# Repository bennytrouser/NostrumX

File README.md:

# NostrumX
A 32 key ergonomic split keyboard using Seeed Xiao BLE

This keyboard is a variation on my original [Nostrum](https://github.com/bennytrouser/nostrum) using a Seeeduino Xiao BLE with the battery mounted under the PCB within the case. Not designed to be used without the case.

The aim was to create a case based board while maintaining as much of the original shape and clean lines of the original nostrum pcb. 

- 3° Splay on pinky and ring columns
- Choc V1 switch compatible (hotswap or soldered). Hotswap recomennded as the switch plate is integrated into the case.
- Custom mildly tented case including switch sliders.
- MCU not socketed, SMD soldered only.
- Created with the [ergogen](https://github.com/ergogen/ergogen) and KiCad8. Case files created with Autodesk Fusion360.
- Firmware using ZMK, including the RGB Widget module from [Caksoylar](https://github.com/caksoylar/zmk-rgbled-widget)
- Inspiration from the [Hummingbird](https://github.com/PJE66/hummingbird) style [Berylline](https://github.com/jcmkk3/trochilidae#berylline) by [jcmkk3](https://github.com/jcmkk3)
- Mousebite breakaway tabs design are inspired by Sadekbaroudi's [bykeeb](https://github.com/sadekbaroudi/bykeeb)

## PCB

## Parts
The case is designed to be fastened from the underside using M1.5x6mm self tapping screws. Feet used are 10x3x1.5mm and 14x3x1.5mm. Left side has space to fit a lipo Battery 402030(180mah). Due to constraints, the right side will need a narrower battery if using hotswap. For my build, I used a 401322 (120mah) but a different size may fit. Example parts listed below. Source your switches and sockets and MCUs where available.

| Part  | Link |
| ------------- | ------------- |
| Battery 402030 | https://www.ebay.co.uk/itm/355875616696 |
| Battery 401322 | https://www.ebay.co.uk/itm/195234785175 |
| Self tapping Screws M1.5x6mm | https://www.aliexpress.com/item/1005005469153402.html |
| SMD diodes SOD-123 1N4148W T4 | https://www.aliexpress.com/item/32948518338.html |
| 1.5mm Fibreoptic cable (for led shinethrough) | https://www.aliexpress.com/item/1005005886250822.html |
| Reset button TL3342 | https://www.aliexpress.com/item/1005007506687094.html |
| Power switch PCM12 | https://www.aliexpress.com/item/32912838968.html |
| Feet | https://www.aliexpress.com/item/1005006691343859.html |

## Case files
Designed in Fusion360. 3d printed. Recommended to print the top case with face down for texured finish. There are two different bottoms, with or without a hole for a reset switch depending on if you want to use one.

The Switch bits need to be fitted before installing the pcb and are a tight fit. Also may require a bit of jiggling to get the slider to seat correctly on install.

The holes on the top of the case allow the charge led and the user led to shine through. I have used fibre optic cable in these holes but it is optional and a tight fit that may require slight enlargement with a screwdriver or small drillbit for the cable to slide in. Any larger in the file and it's a little loose.

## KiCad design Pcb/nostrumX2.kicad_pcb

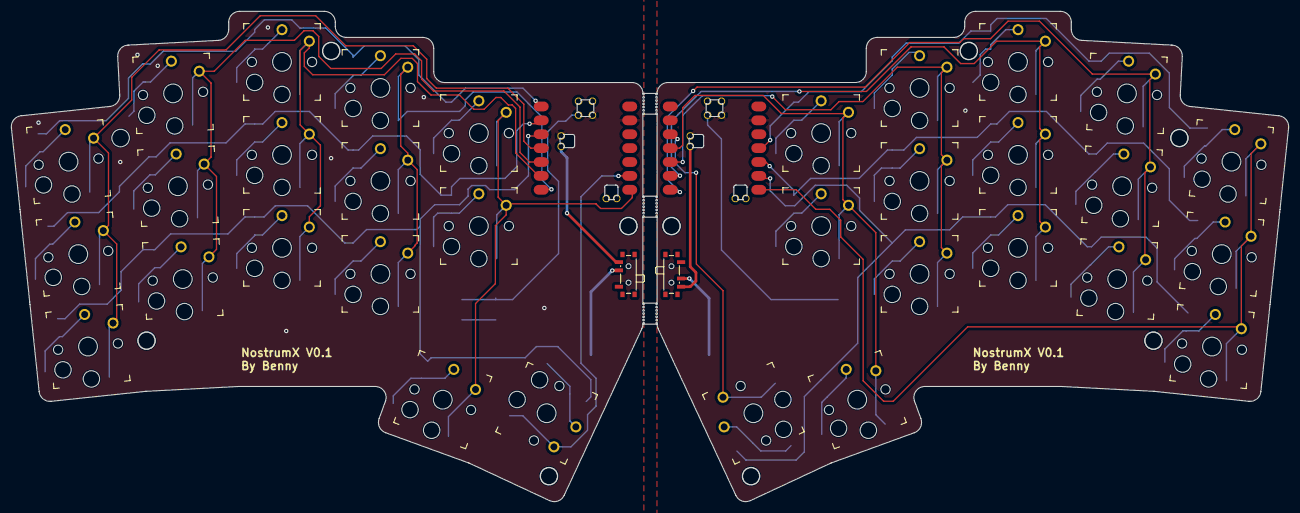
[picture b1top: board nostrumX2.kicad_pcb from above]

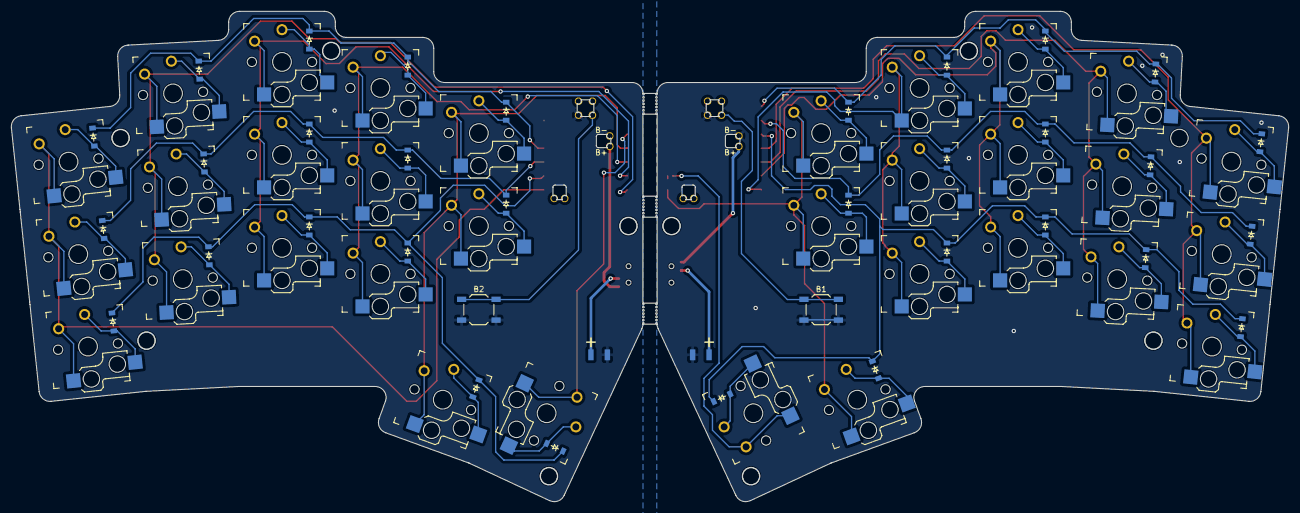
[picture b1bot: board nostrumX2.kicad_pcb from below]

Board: 2 copper layers, 233.6 x 89.7 mm, 79 parts (34 on the bottom side), 52 nets.

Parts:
B1, B2: SW_SPST_TL3342
D1, D2, D3, D4, D5, D6, D7, D8, D9, D10, D11, D12, D13, D14, D15, D16, D17, D18, D19, D20, D21, D22, D23, D24, D25, D26, D27, D28, D29, D30, D31, D32: ComboDiode
LH1, LH2, LH3: Breakaway Tabs; Breakaway_Tabs_Med
Mount: MountingHole_3.2mm_M3
PAD1, PAD2, PAD3, PAD4: SMDPad
RH1, RH2, RH3: Breakaway Tabs; Breakaway_Tabs_Med
S1, S2, S3, S4, S5, S6, S7, S8, S9, S10, S11, S12, S13, S14, S15, S16, S17, S18, S19, S20, S21, S22, S23, S24, S25, S26, S27, S28, S29, S30, S31, S32: PG1350
SW1, SW2: SW_SPDT_PCM12

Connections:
C0: S1.1, S2.1, S3.1
C1: S4.1, S5.1, S6.1
C2: S7.1, S8.1, S9.1
C3: S10.1, S11.1, S12.1
C4: S13.1, S14.1, S29.1
GND: B1.2, PAD2.1
MC0: S15.1, S16.1, S17.1
MC1: S18.1, S19.1, S20.1
MC2: S21.1, S22.1, S23.1
MC3: S24.1, S25.1, S26.1
MC4: S27.1, S28.1, S31.1
MGND: B2.2, PAD4.1
MR0: D19.1, D22.1, D25.1, D28.1, D30.1
MR1: D18.1, D21.1, D24.1, D27.1, D29.1
MR2: D17.1, D20.1, D23.1, D26.1, D31.1, D32.1
Mpos: PAD3.1, SW2.2
R0: D3.1, D6.1, D9.1, D12.1, D14.1
R1: D2.1, D5.1, D8.1, D11.1, D13.1
R2: D1.1, D4.1, D7.1, D10.1, D15.1, D16.1
index_bottom: D10.2, S10.2
index_home: D11.2, S11.2
index_top: D12.2, S12.2
inner_bottom: D13.2, S13.2
inner_home: D14.2, S14.2
left_home: D15.2, S29.2
middle_bottom: D7.2, S7.2
middle_home: D8.2, S8.2
middle_top: D9.2, S9.2
mirror_index_bottom: D26.2, S24.2
mirror_index_home: D27.2, S25.2
mirror_index_top: D28.2, S26.2
mirror_inner_bottom: D29.2, S27.2
mirror_inner_home: D30.2, S28.2
mirror_left_home: D31.2, S31.2
mirror_middle_bottom: D23.2, S21.2
mirror_middle_home: D24.2, S22.2
mirror_middle_top: D25.2, S23.2
mirror_pinky_bottom: D17.2, S15.2
mirror_pinky_home: D18.2, S16.2
mirror_pinky_top: D19.2, S17.2
mirror_right_home: D32.2, S32.2
mirror_ring_bottom: D20.2, S18.2
mirror_ring_home: D21.2, S19.2
mirror_ring_top: D22.2, S20.2
pinky_bottom: D1.2, S1.2
pinky_home: D2.2, S2.2
pinky_top: D3.2, S3.2
pos: PAD1.1, SW1.2
right_home: D16.2, S30.2
ring_bottom: D4.2, S4.2
ring_home: D5.2, S5.2
ring_top: D6.2, S6.2

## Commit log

2024-08-13 Updated files and readme
2024-08-13 update RM
2024-08-15 Final update
2024-08-15 add sadek ref
2024-08-18 rm update
